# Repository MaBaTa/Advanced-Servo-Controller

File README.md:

# Advanced-Servo-Controller

::: warn
Software not finished jet

:::

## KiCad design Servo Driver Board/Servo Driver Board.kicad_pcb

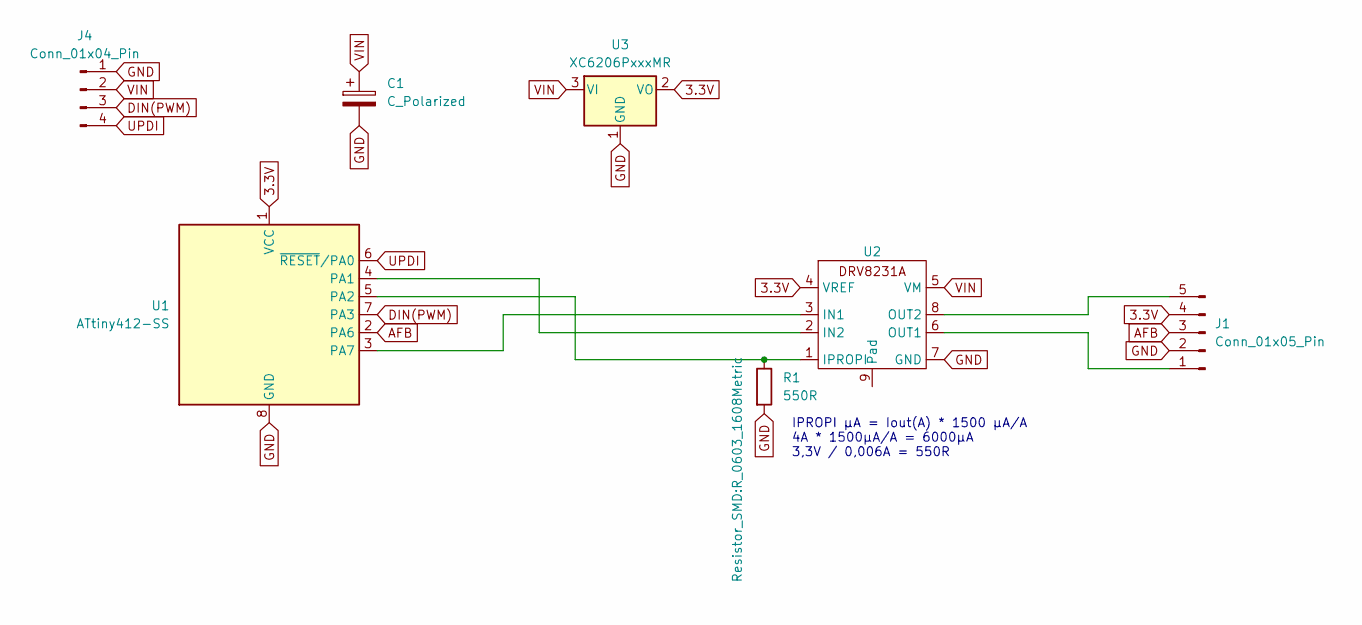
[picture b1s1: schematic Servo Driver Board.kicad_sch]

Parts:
C1: C_Polarized; C_0805_2012Metric
J1: Conn_01x05_Pin; PinHeader_1x05_P1.27mm_Vertical
J4: Conn_01x04_Pin; PinHeader_1x04_P1.27mm_Vertical
R1: 550R; R_0603_1608Metric
U1: ATtiny412-SS; SOIC-8_3.9x4.9mm_P1.27mm
U2: HSOP-8-1EP_3.9x4.9mm_P1.27mm_EP2.41x3.1mm
U3: XC6206PxxxMR; SOT-23-3

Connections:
3.3V: J1.4, U1.1 (VCC), U2.4 (VREF), U3.2 (VO)
AFB: J1.3, U1.2 (PA6)
DIN(PWM): J4.3, U1.7 (PA3)
GND: C1.2, J1.2, J4.1, R1.2, U1.8 (GND), U2.7 (GND), U3.1 (GND)
unnamed: J1.1, U2.6 (OUT1)
unnamed: J1.5, U2.8 (OUT2)
unnamed: U1.4 (PA1), U2.2 (IN2)
unnamed: R1.1, U1.5 (PA2), U2.1 (IPROPI)
unnamed: U1.3 (PA7), U2.3 (IN1)
UPDI: J4.4, U1.6 (~RESET/PA0)
VIN: C1.1, J4.2, U2.5 (VM), U3.3 (VI)

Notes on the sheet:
IPROPI μA = Iout(A) * 1500 μA/A 4A * 1500μA/A = 6000μA 3,3V / 0,006A = 550R

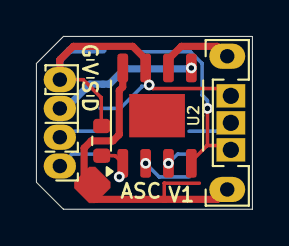
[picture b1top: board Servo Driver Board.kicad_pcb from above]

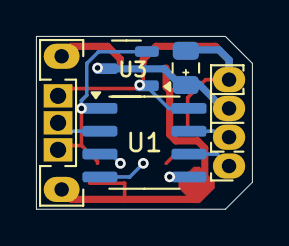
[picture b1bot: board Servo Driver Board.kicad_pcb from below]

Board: 2 copper layers, 12.0 x 9.6 mm, 7 parts (3 on the bottom side), 11 nets.

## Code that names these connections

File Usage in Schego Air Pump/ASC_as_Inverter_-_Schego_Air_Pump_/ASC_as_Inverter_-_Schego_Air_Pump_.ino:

#include <megaTinyCore.h>

#define MOTOR_PWM1_PIN PIN_PA7
#define MOTOR_PWM2_PIN PIN_PA1
#define MOTOR_IPROPI_PIN PIN_PA2
#define POTI_POS_PIN PIN_PA6
#define PWM_IN_PIN PIN_PA3
//DO NOT USE UPDI PA0

//Rect Wave
#define freqency  45
#define power  0.8

int input = 0;

void setup() {
  pinMode(MOTOR_PWM1_PIN, OUTPUT);
  pinMode(MOTOR_PWM2_PIN, OUTPUT);
  //analogWriteFreq(200000);
  pinMode(MOTOR_IPROPI_PIN, INPUT);
  analogReference(VDD); //INTERNAL2V5
  
  digitalWrite(MOTOR_PWM1_PIN, LOW);
  digitalWrite(MOTOR_PWM2_PIN, LOW);

}

void loop() {

  analogWrite(MOTOR_PWM1_PIN, 255);
  analogWrite(MOTOR_PWM2_PIN, 0);
  delayMicroseconds((1000000/freqency)/2*power);
  analogWrite(MOTOR_PWM1_PIN, 0);
  analogWrite(MOTOR_PWM2_PIN, 0);
  delayMicroseconds((1000000/freqency)/2*(1-power));
  analogWrite(MOTOR_PWM1_PIN, 0);
  analogWrite(MOTOR_PWM2_PIN, 255);
  delayMicroseconds((1000000/freqency)/2*power);
  analogWrite(MOTOR_PWM1_PIN, 0);
  analogWrite(MOTOR_PWM2_PIN, 0);
  delayMicroseconds((1000000/freqency)/2*(1-power));
}

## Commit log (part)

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2025-06-02 Initial_Commit
2025-06-17 Working Code
2025-11-15 Init Air Pump
2025-11-15 Doku
2025-11-15 ASC as Inverter Documentation
2026-01-29 Schego Air Pump spelling improved
2026-03-15 PID Experiments
2026-03-15 Exported
2026-03-15 Proxxon Micromot
